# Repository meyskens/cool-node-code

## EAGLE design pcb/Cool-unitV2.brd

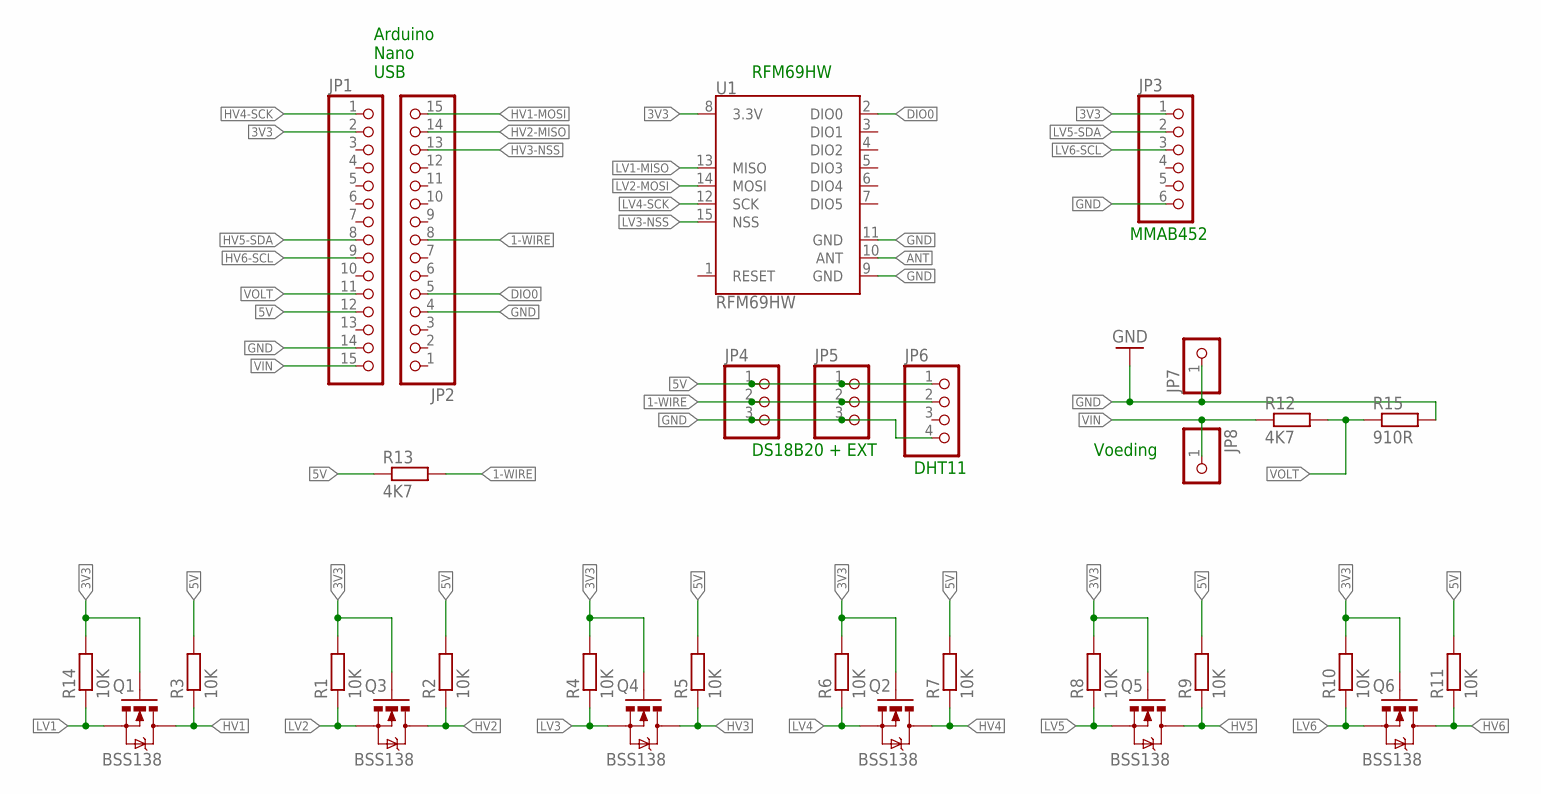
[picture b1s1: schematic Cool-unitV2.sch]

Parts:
JP1, JP2: PINHD-1X15; 1X15
JP3: PINHD-1X6; 1X06
JP4, JP5: PINHD-1X3; 1X03
JP6: PINHD-1X4; 1X04
JP7, JP8: PINHD-1X1; 1X01
Q1, Q2, Q3, Q4, Q5, Q6: BSS138; SOT23-3
R1, R2, R3, R4, R5, R6, R7, R8, R9, R10, R11, R14: 10K; R3216
R12, R13: 4K7; R3216
R15: 910R; R3216
U1: RFM69HW; RFM69W-XXXS2

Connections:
1-WIRE: JP2.8, JP4.2, JP5.2, JP6.2, R13.2
3V3: JP1.2, JP3.1, Q1.1 (G), Q2.1 (G), Q3.1 (G), Q4.1 (G), Q5.1 (G), Q6.1 (G), R1.2, R4.2, R6.2, R8.2, R10.2, R14.2, U1.8 (3.3V)
5V: JP1.12, JP4.1, JP5.1, JP6.1, R2.2, R3.2, R5.2, R7.2, R9.2, R11.2, R13.1
ANT: U1.10 (ANT)
DIO0: JP2.5, U1.2 (DIO0)
GND: JP1.14, JP2.4, JP3.6, JP4.3, JP5.3, JP6.4, JP7.1, R15.2, U1.9 (GND), U1.11 (GND)
HV1: JP2.15, Q1.3 (D), R3.1
HV2: JP2.14, Q3.3 (D), R2.1
HV3: JP2.13, Q4.3 (D), R5.1
HV4: JP1.1, Q2.3 (D), R7.1
HV5: JP1.8, Q5.3 (D), R9.1
HV6: JP1.9, Q6.3 (D), R11.1
LV1: Q1.2 (S), R14.1, U1.13 (MISO)
LV2: Q3.2 (S), R1.1, U1.14 (MOSI)
LV3: Q4.2 (S), R4.1, U1.15 (NSS)
LV4: Q2.2 (S), R6.1, U1.12 (SCK)
LV5: JP3.2, Q5.2 (S), R8.1
LV6: JP3.3, Q6.2 (S), R10.1
VIN: JP1.15, JP8.1, R12.1
VOLT: JP1.11, R12.2, R15.1

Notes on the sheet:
Arduino Nano USB
RFM69HW
MMAB452
DS18B20 + EXT
DHT11
Voeding

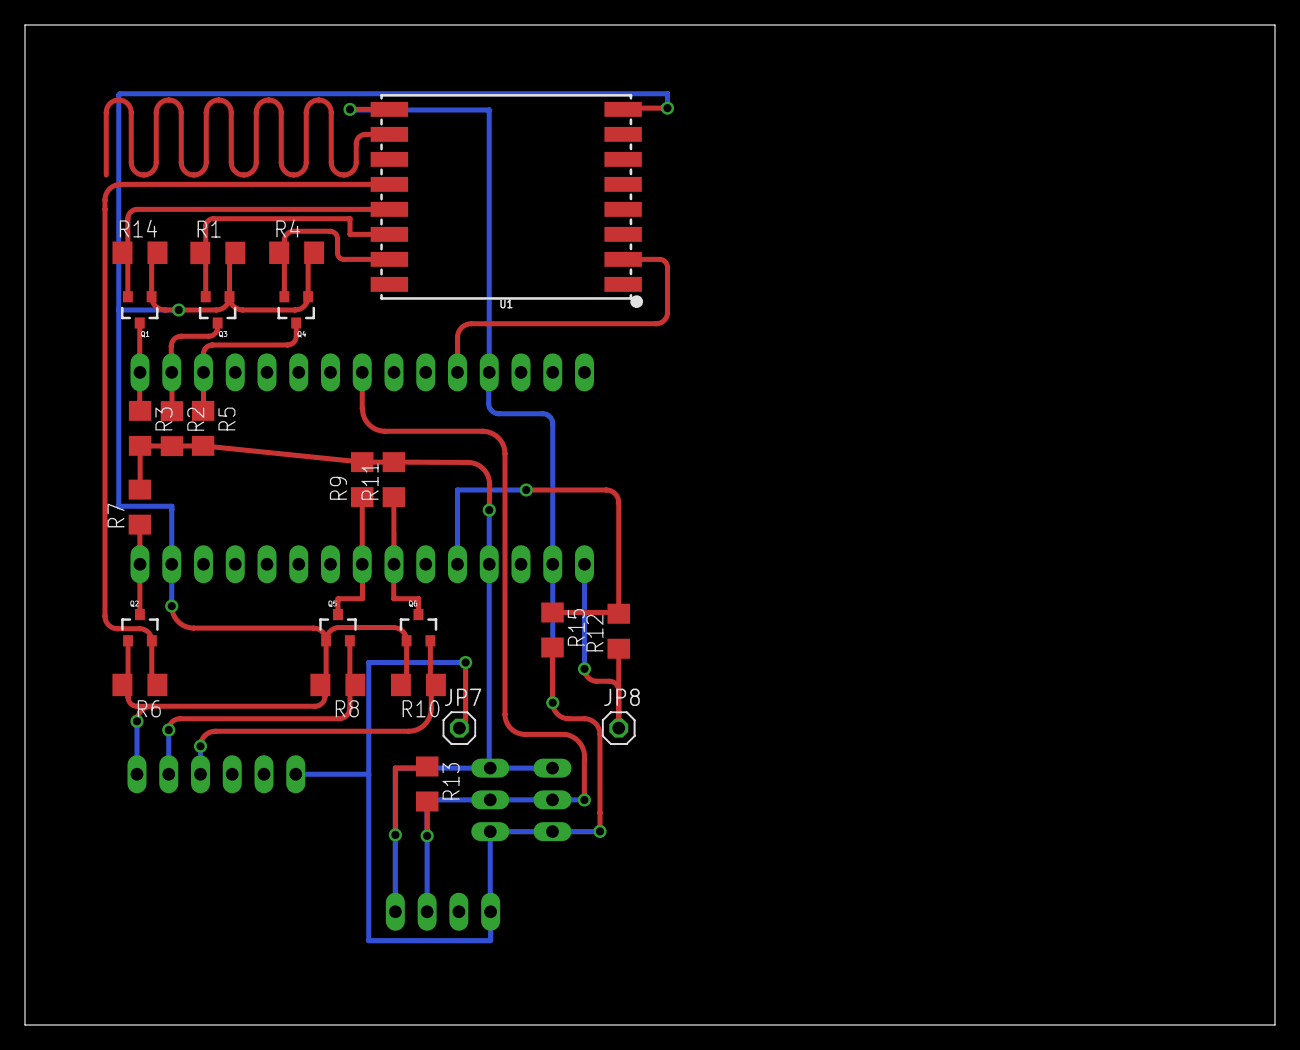
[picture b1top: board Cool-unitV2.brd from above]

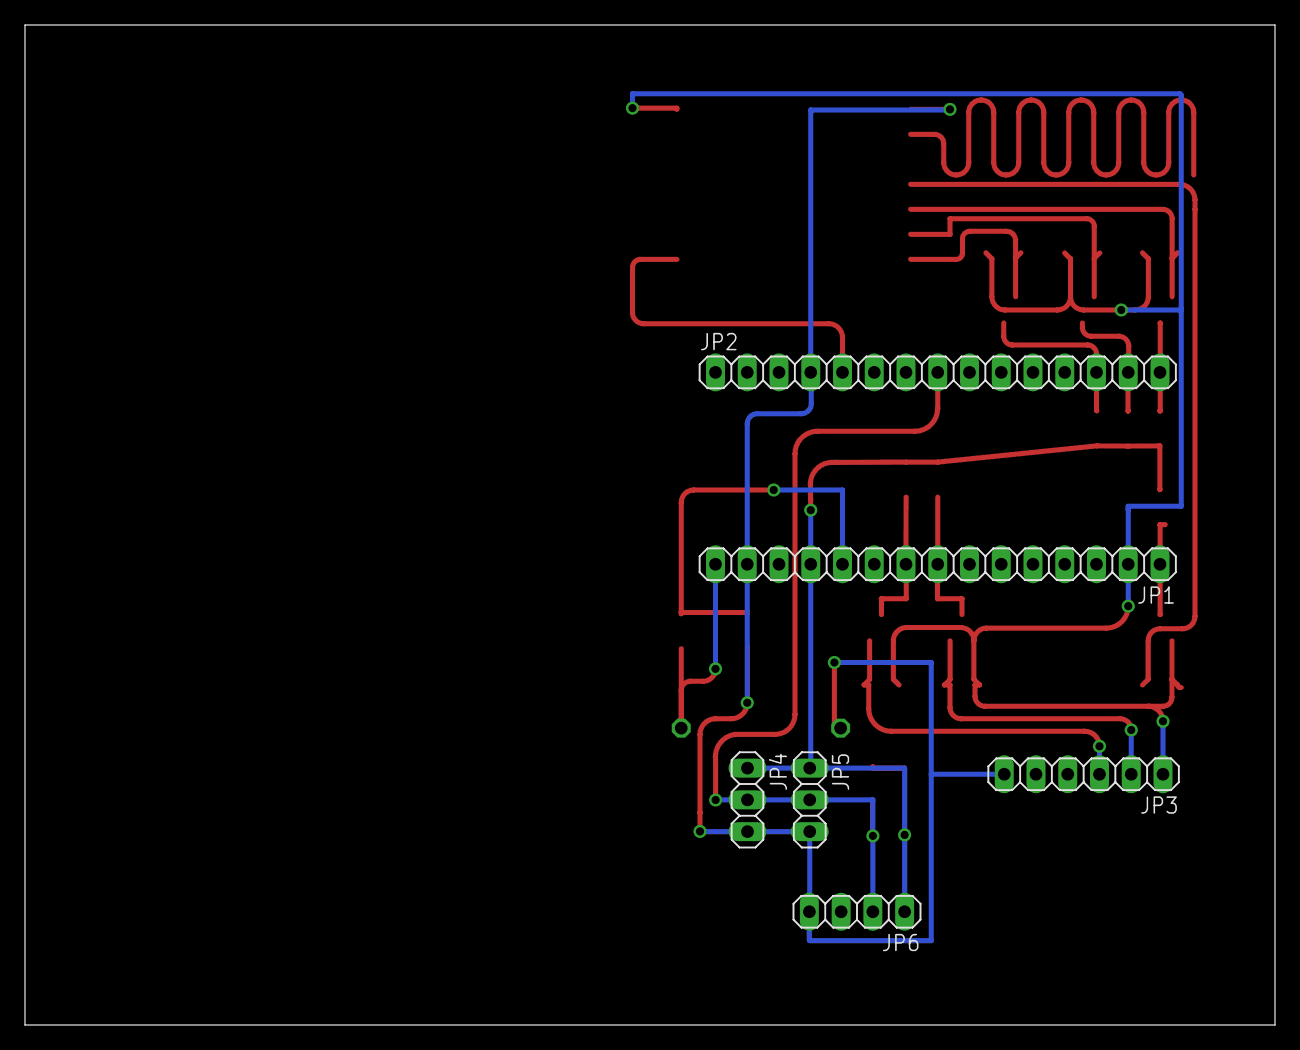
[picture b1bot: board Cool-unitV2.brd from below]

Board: 2 copper layers, 100.0 x 80.0 mm, 30 parts (6 on the bottom side), 19 nets.

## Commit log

2017-10-26 go GPL for libraries
2017-11-01 initial commot
2017-11-01 fix misplaced error
2017-11-07 use prinln
2017-11-07 test 2
2017-11-15 add ram test
2017-11-15 add for loop test
2017-11-15 try to modify struct data
2017-11-15 fix loop?
2017-11-25 add stringtest
2017-11-25 add stringtest to yml
2017-12-10 add node code
2017-12-10 rm test file
2017-12-28 final code
2017-12-28 add pcb

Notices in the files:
parts and their libraries:
SparkFun-RF: Licensing: Creative Commons ShareAlike 4.0 International - https://creativecommons.org/licenses/by-sa/4.0
